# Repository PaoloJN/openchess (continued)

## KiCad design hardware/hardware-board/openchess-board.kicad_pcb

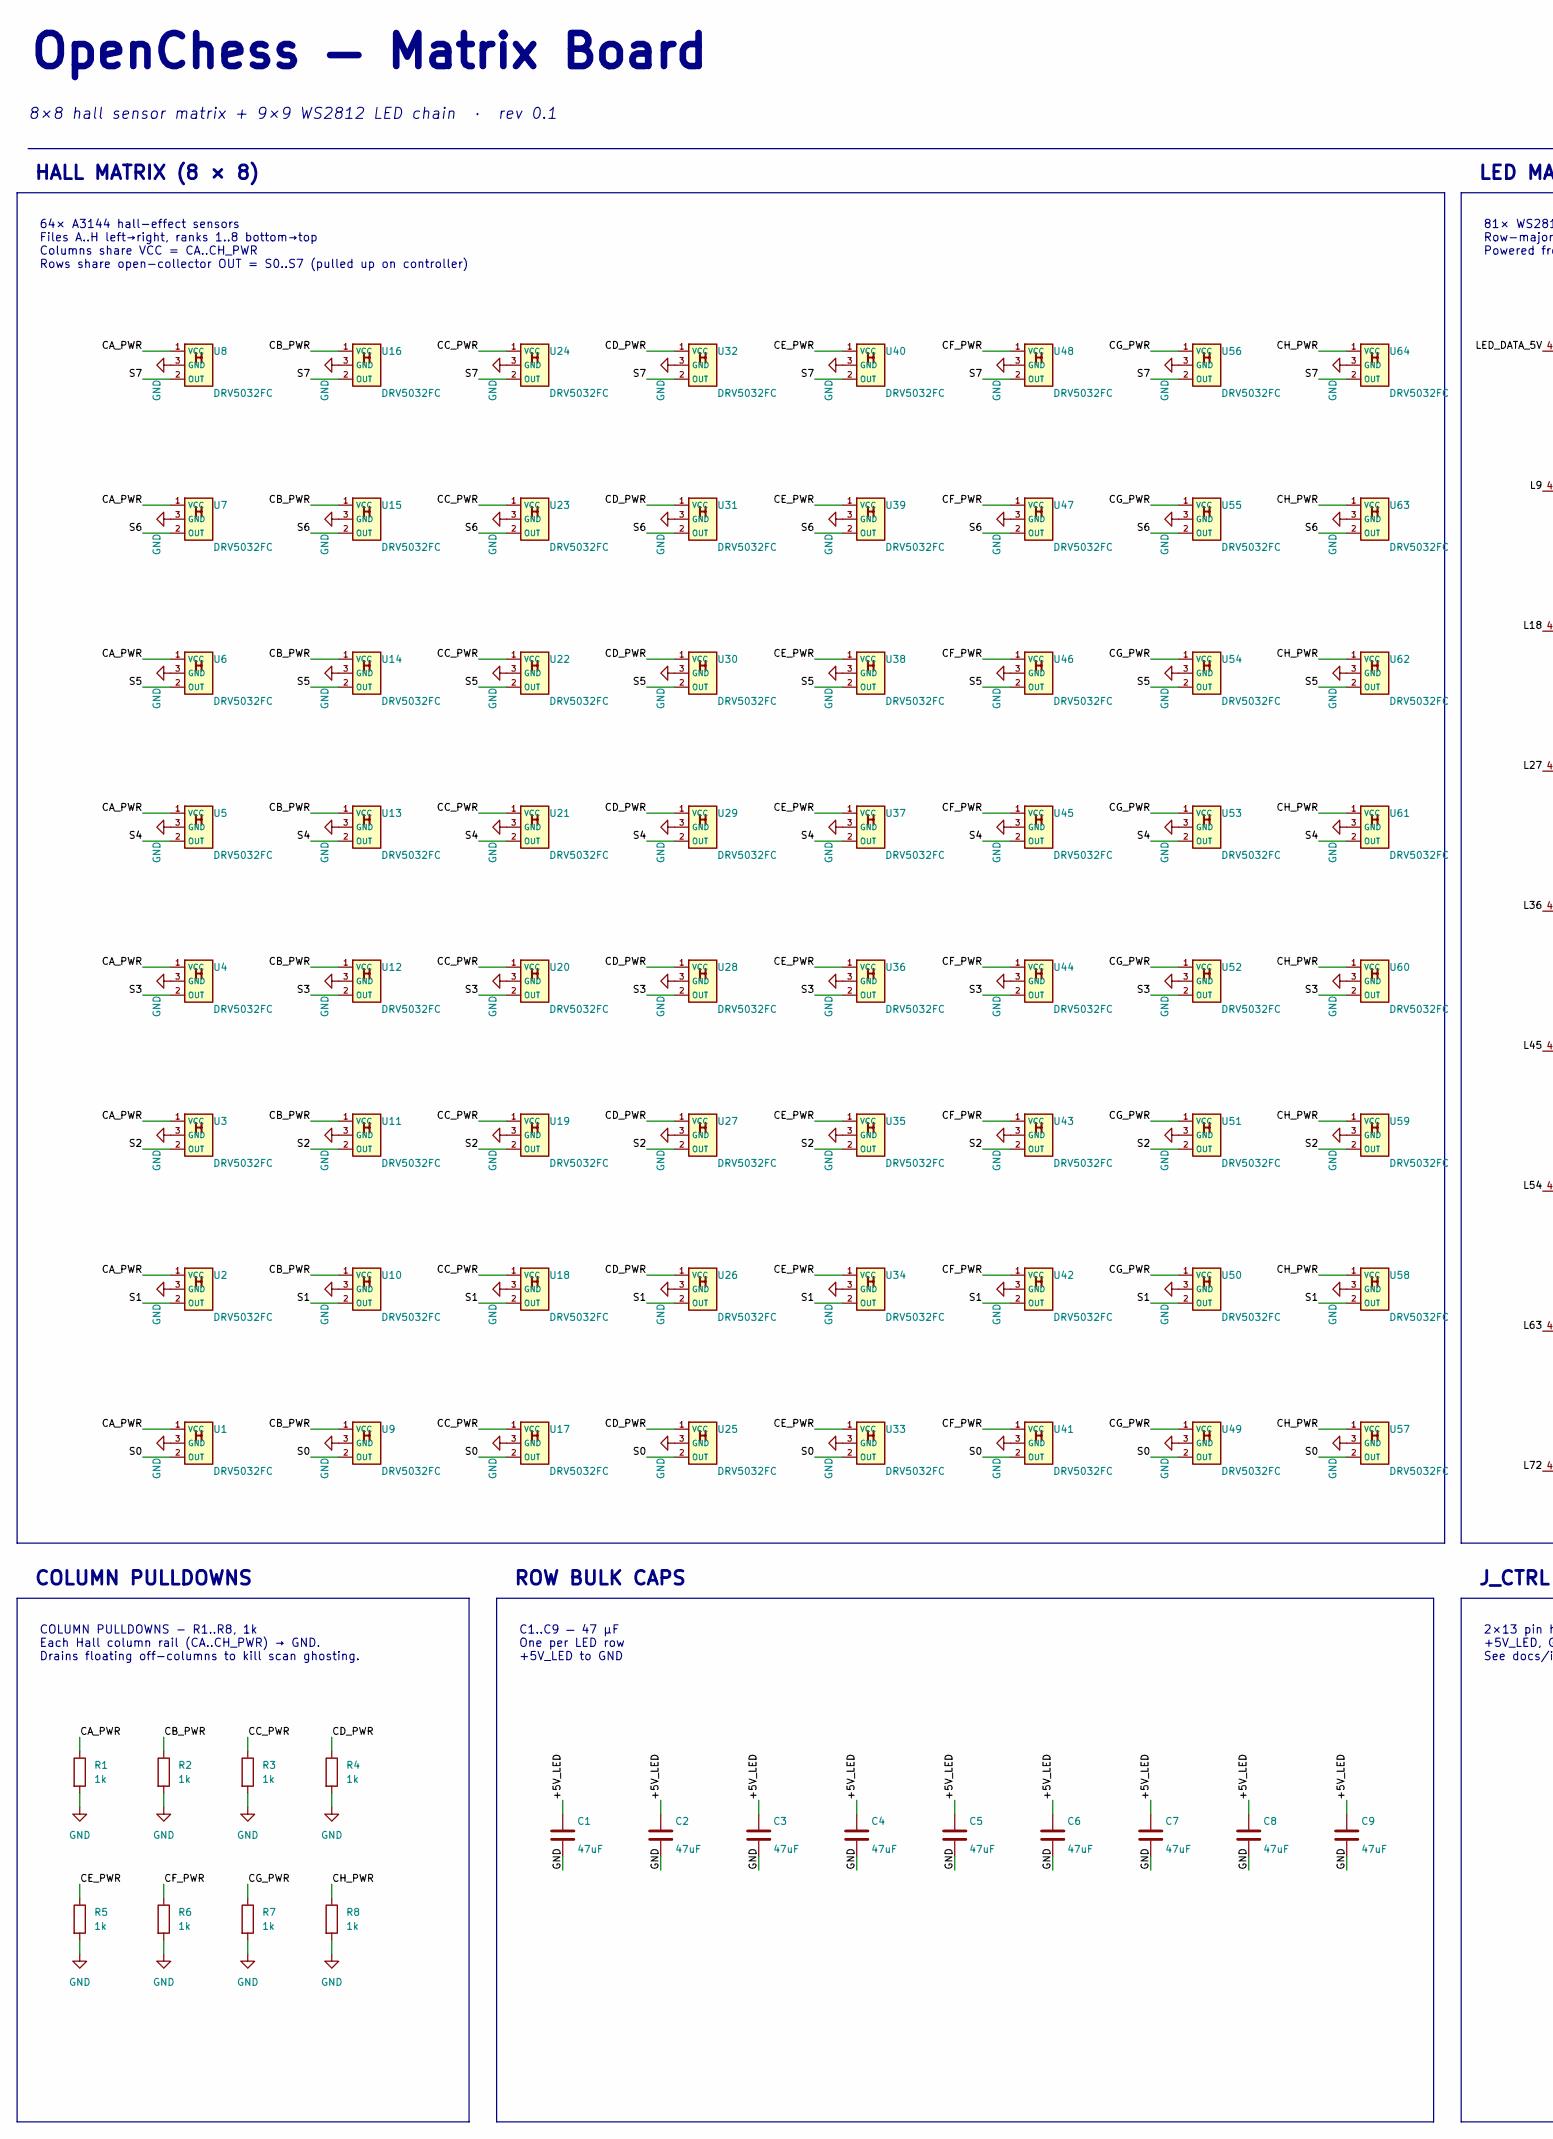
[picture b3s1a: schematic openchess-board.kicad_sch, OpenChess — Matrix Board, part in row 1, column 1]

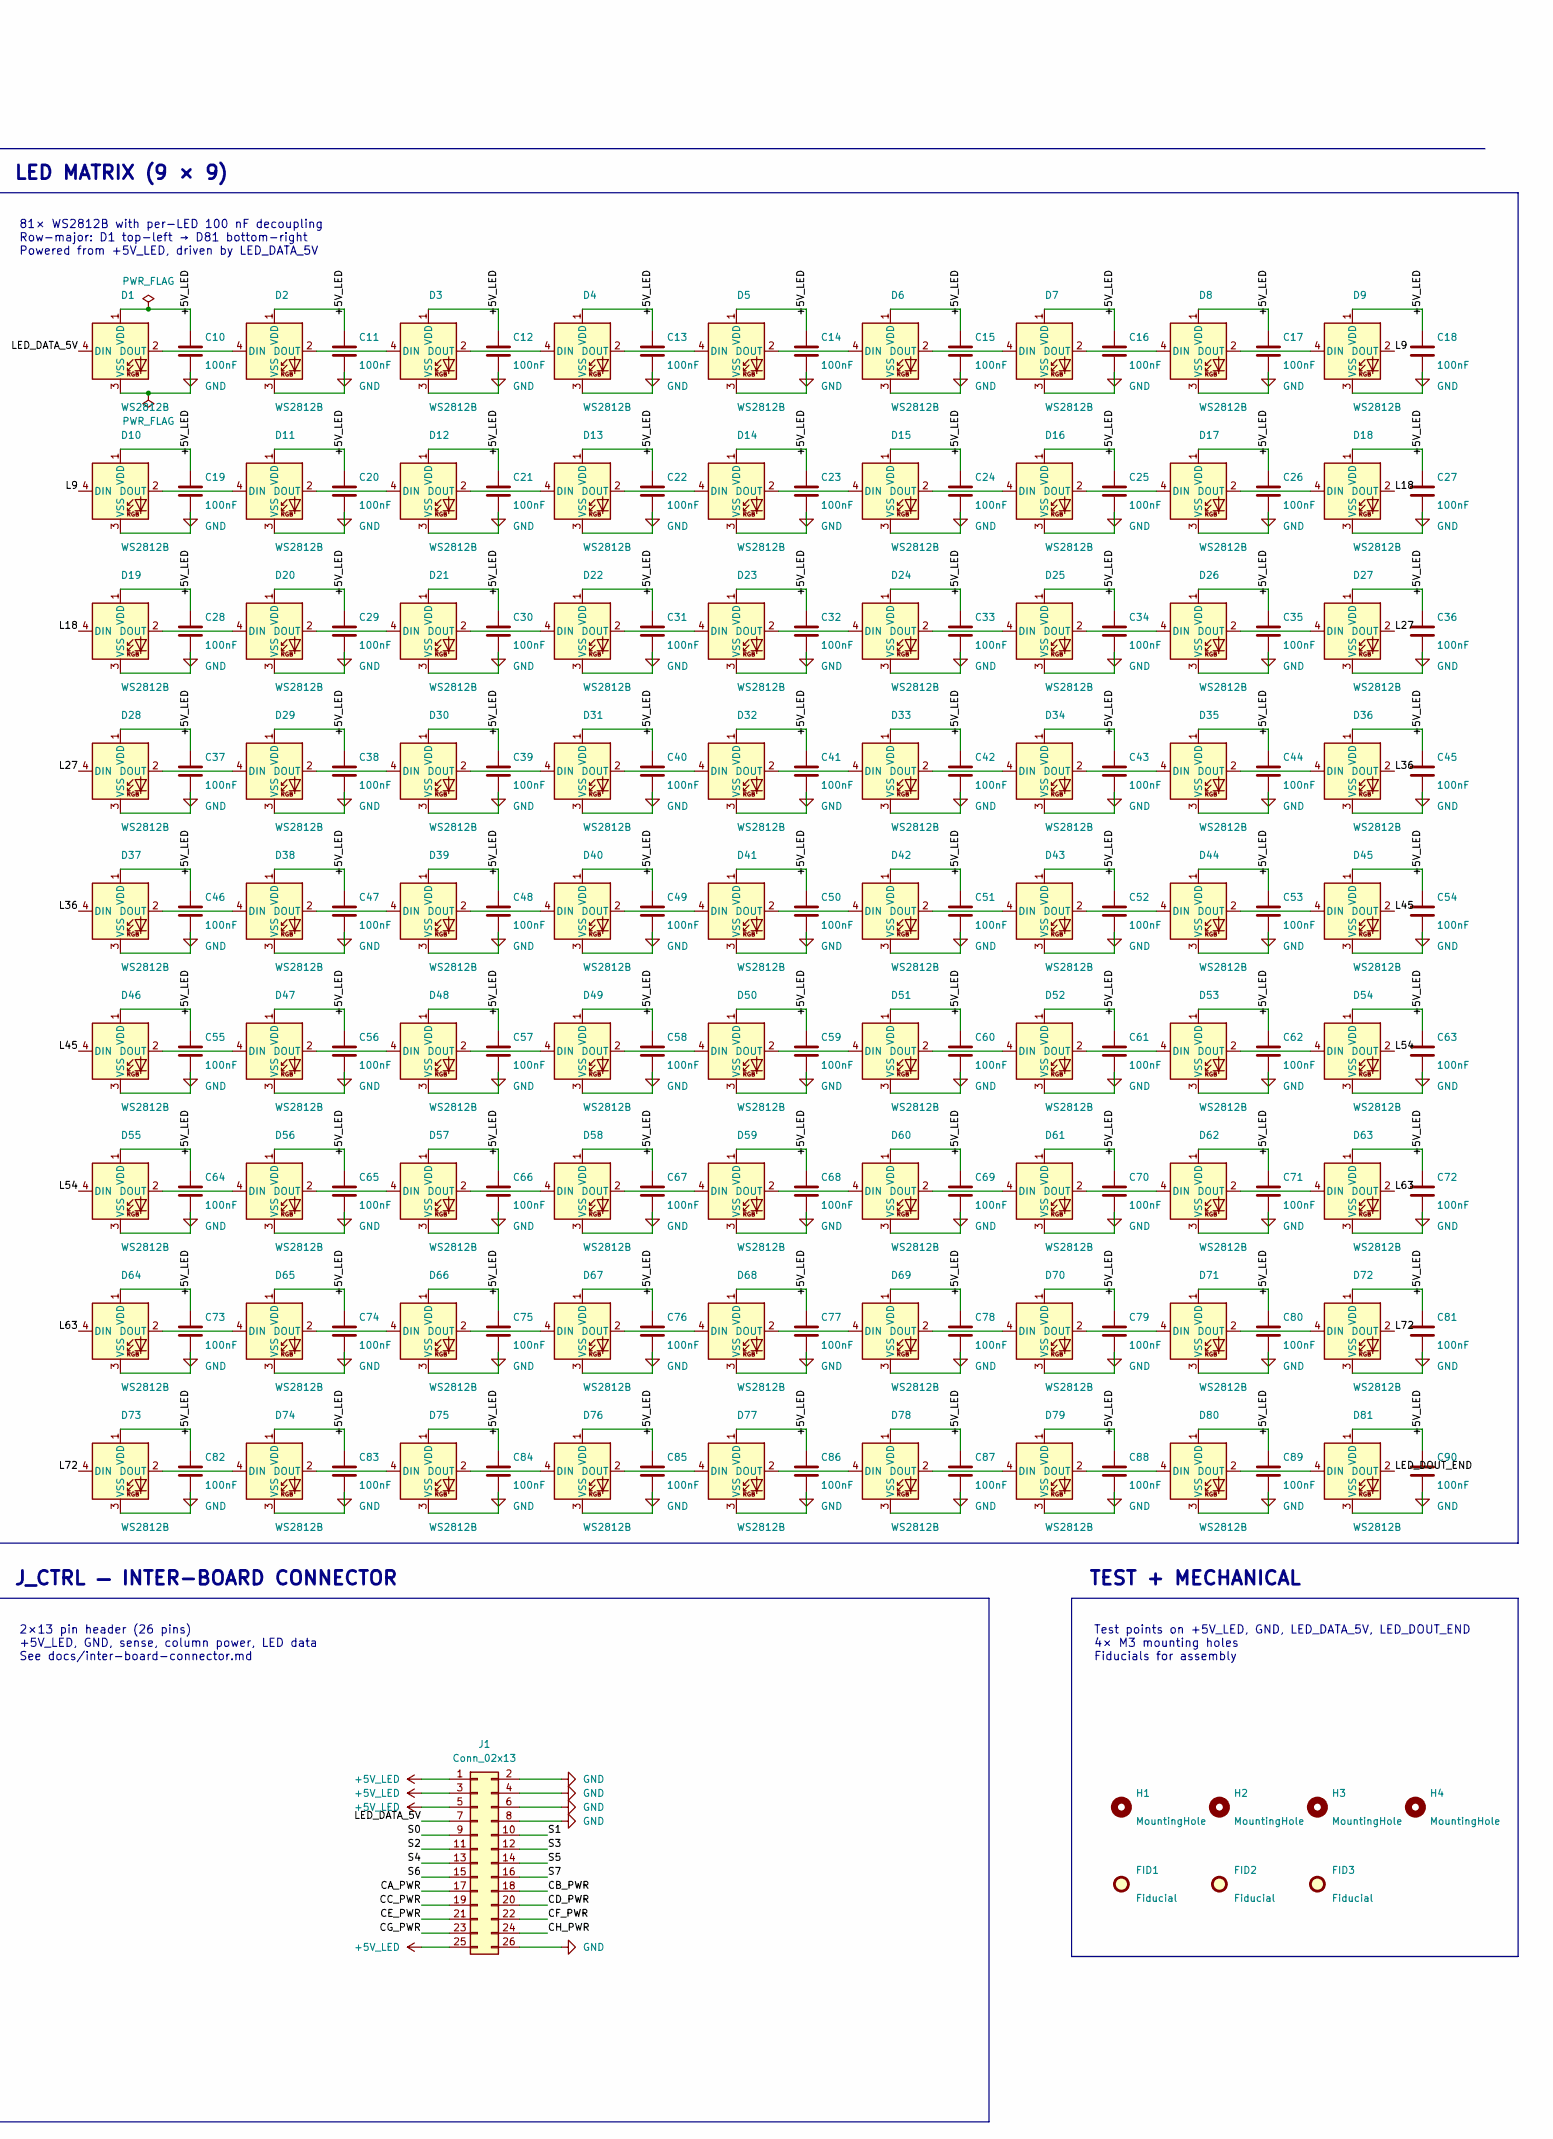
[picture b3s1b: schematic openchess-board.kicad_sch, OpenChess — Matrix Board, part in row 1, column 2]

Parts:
C1, C2, C3, C4, C5, C6, C7, C8, C9: 47uF; C_1206_3216Metric
C10, C11, C12, C13, C14, C15, C16, C17, C18, C19, C20, C21, C22, C23, C24, C25, C26, C27, C28, C29, C30, C31, C32, C33, C34, C35, C36, C37, C38, C39, C40, C41, C42, C43, C44, C45, C46, C47, C48, C49, C50, C51, C52, C53, C54, C55, C56, C57, C58, C59, C60, C61, C62, C63, C64, C65, C66, C67, C68, C69, C70, C71, C72, C73, C74, C75, C76, C77, C78, C79, C80, C81, C82, C83, C84, C85, C86, C87, C88, C89, C90: 100nF; C_0805_2012Metric_Pad1.18x1.45mm_HandSolder
D1, D2, D3, D4, D5, D6, D7, D8, D9, D10, D11, D12, D13, D14, D15, D16, D17, D18, D19, D20, D21, D22, D23, D24, D25, D26, D27, D28, D29, D30, D31, D32, D33, D34, D35, D36, D37, D38, D39, D40, D41, D42, D43, D44, D45, D46, D47, D48, D49, D50, D51, D52, D53, D54, D55, D56, D57, D58, D59, D60, D61, D62, D63, D64, D65, D66, D67, D68, D69, D70, D71, D72, D73, D74, D75, D76, D77, D78, D79, D80, D81: WS2812B; LED_WS2812B_PLCC4_5.0x5.0mm_P3.2mm
FID1, FID2, FID3: Fiducial; Fiducial_1mm_Mask2mm
H1, H2, H3, H4: MountingHole; MountingHole_3.2mm_M3
J1: Conn_02x13; PinHeader_2x13_P2.54mm_Vertical
R1, R2, R3, R4, R5, R6, R7, R8: 1k; R_0805_2012Metric_Pad1.20x1.40mm_HandSolder
U1, U2, U3, U4, U5, U6, U7, U8, U9, U10, U11, U12, U13, U14, U15, U16, U17, U18, U19, U20, U21, U22, U23, U24, U25, U26, U27, U28, U29, U30, U31, U32, U33, U34, U35, U36, U37, U38, U39, U40, U41, U42, U43, U44, U45, U46, U47, U48, U49, U50, U51, U52, U53, U54, U55, U56, U57, U58, U59, U60, U61, U62, U63, U64: DRV5032FC; SOT-23

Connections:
+5V_LED: C1.1, C2.1, C3.1, C4.1, C5.1, C6.1, C7.1, C8.1, C9.1, C10.1, C11.1, C12.1, C13.1, C14.1, C15.1, C16.1, C17.1, C18.1, C19.1, C20.1, C21.1, C22.1, C23.1, C24.1, C25.1, C26.1, C27.1, C28.1, C29.1, C30.1, C31.1, C32.1, C33.1, C34.1, C35.1, C36.1, C37.1, C38.1, C39.1, C40.1, C41.1, C42.1, C43.1, C44.1, C45.1, C46.1, C47.1, C48.1, C49.1, C50.1, C51.1, C52.1, C53.1, C54.1, C55.1, C56.1, C57.1, C58.1, C59.1, C60.1, C61.1, C62.1, C63.1, C64.1, C65.1, C66.1, C67.1, C68.1, C69.1, C70.1, C71.1, C72.1, C73.1, C74.1, C75.1, C76.1, C77.1, C78.1, C79.1, C80.1, C81.1, C82.1, C83.1, C84.1, C85.1, C86.1, C87.1, C88.1, C89.1, C90.1, D1.1 (VDD), D2.1 (VDD), D3.1 (VDD), D4.1 (VDD), D5.1 (VDD), D6.1 (VDD), D7.1 (VDD), D8.1 (VDD), D9.1 (VDD), D10.1 (VDD), D11.1 (VDD), D12.1 (VDD), D13.1 (VDD), D14.1 (VDD), D15.1 (VDD), D16.1 (VDD), D17.1 (VDD), D18.1 (VDD), D19.1 (VDD), D20.1 (VDD), D21.1 (VDD), D22.1 (VDD), D23.1 (VDD), D24.1 (VDD), D25.1 (VDD), D26.1 (VDD), D27.1 (VDD), D28.1 (VDD), D29.1 (VDD), D30.1 (VDD), D31.1 (VDD), D32.1 (VDD), D33.1 (VDD), D34.1 (VDD), D35.1 (VDD), D36.1 (VDD), D37.1 (VDD), D38.1 (VDD), D39.1 (VDD), D40.1 (VDD), D41.1 (VDD), D42.1 (VDD), D43.1 (VDD), D44.1 (VDD), D45.1 (VDD), D46.1 (VDD), D47.1 (VDD), D48.1 (VDD), D49.1 (VDD), D50.1 (VDD), D51.1 (VDD), D52.1 (VDD), D53.1 (VDD), D54.1 (VDD), D55.1 (VDD), D56.1 (VDD), D57.1 (VDD), D58.1 (VDD), D59.1 (VDD), D60.1 (VDD), D61.1 (VDD), D62.1 (VDD), D63.1 (VDD), D64.1 (VDD), D65.1 (VDD), D66.1 (VDD), D67.1 (VDD), D68.1 (VDD), D69.1 (VDD), D70.1 (VDD), D71.1 (VDD), D72.1 (VDD), D73.1 (VDD), D74.1 (VDD), D75.1 (VDD), D76.1 (VDD), D77.1 (VDD), D78.1 (VDD), D79.1 (VDD), D80.1 (VDD), D81.1 (VDD), J1.1, J1.3, J1.5, J1.25
/CA_PWR: J1.17, R1.1, U1.1 (VCC), U2.1 (VCC), U3.1 (VCC), U4.1 (VCC), U5.1 (VCC), U6.1 (VCC), U7.1 (VCC), U8.1 (VCC)
/CB_PWR: J1.18, R2.1, U9.1 (VCC), U10.1 (VCC), U11.1 (VCC), U12.1 (VCC), U13.1 (VCC), U14.1 (VCC), U15.1 (VCC), U16.1 (VCC)
/CC_PWR: J1.19, R3.1, U17.1 (VCC), U18.1 (VCC), U19.1 (VCC), U20.1 (VCC), U21.1 (VCC), U22.1 (VCC), U23.1 (VCC), U24.1 (VCC)
/CD_PWR: J1.20, R4.1, U25.1 (VCC), U26.1 (VCC), U27.1 (VCC), U28.1 (VCC), U29.1 (VCC), U30.1 (VCC), U31.1 (VCC), U32.1 (VCC)
/CE_PWR: J1.21, R5.1, U33.1 (VCC), U34.1 (VCC), U35.1 (VCC), U36.1 (VCC), U37.1 (VCC), U38.1 (VCC), U39.1 (VCC), U40.1 (VCC)
/CF_PWR: J1.22, R6.1, U41.1 (VCC), U42.1 (VCC), U43.1 (VCC), U44.1 (VCC), U45.1 (VCC), U46.1 (VCC), U47.1 (VCC), U48.1 (VCC)
/CG_PWR: J1.23, R7.1, U49.1 (VCC), U50.1 (VCC), U51.1 (VCC), U52.1 (VCC), U53.1 (VCC), U54.1 (VCC), U55.1 (VCC), U56.1 (VCC)
/CH_PWR: J1.24, R8.1, U57.1 (VCC), U58.1 (VCC), U59.1 (VCC), U60.1 (VCC), U61.1 (VCC), U62.1 (VCC), U63.1 (VCC), U64.1 (VCC)
/L9: D9.2 (DOUT), D10.4 (DIN)
/L18: D18.2 (DOUT), D19.4 (DIN)
/L27: D27.2 (DOUT), D28.4 (DIN)
/L36: D36.2 (DOUT), D37.4 (DIN)
/L45: D45.2 (DOUT), D46.4 (DIN)
/L54: D54.2 (DOUT), D55.4 (DIN)
/L63: D63.2 (DOUT), D64.4 (DIN)
/L72: D72.2 (DOUT), D73.4 (DIN)
/LED_DATA_5V: D1.4 (DIN), J1.7
/LED_DOUT_END: D81.2 (DOUT)
/S0: J1.9, U1.2 (OUT), U9.2 (OUT), U17.2 (OUT), U25.2 (OUT), U33.2 (OUT), U41.2 (OUT), U49.2 (OUT), U57.2 (OUT)
/S1: J1.10, U2.2 (OUT), U10.2 (OUT), U18.2 (OUT), U26.2 (OUT), U34.2 (OUT), U42.2 (OUT), U50.2 (OUT), U58.2 (OUT)
/S2: J1.11, U3.2 (OUT), U11.2 (OUT), U19.2 (OUT), U27.2 (OUT), U35.2 (OUT), U43.2 (OUT), U51.2 (OUT), U59.2 (OUT)
/S3: J1.12, U4.2 (OUT), U12.2 (OUT), U20.2 (OUT), U28.2 (OUT), U36.2 (OUT), U44.2 (OUT), U52.2 (OUT), U60.2 (OUT)
/S4: J1.13, U5.2 (OUT), U13.2 (OUT), U21.2 (OUT), U29.2 (OUT), U37.2 (OUT), U45.2 (OUT), U53.2 (OUT), U61.2 (OUT)
/S5: J1.14, U6.2 (OUT), U14.2 (OUT), U22.2 (OUT), U30.2 (OUT), U38.2 (OUT), U46.2 (OUT), U54.2 (OUT), U62.2 (OUT)
/S6: J1.15, U7.2 (OUT), U15.2 (OUT), U23.2 (OUT), U31.2 (OUT), U39.2 (OUT), U47.2 (OUT), U55.2 (OUT), U63.2 (OUT)
/S7: J1.16, U8.2 (OUT), U16.2 (OUT), U24.2 (OUT), U32.2 (OUT), U40.2 (OUT), U48.2 (OUT), U56.2 (OUT), U64.2 (OUT)
GND: C1.2, C2.2, C3.2, C4.2, C5.2, C6.2, C7.2, C8.2, C9.2, C10.2, C11.2, C12.2, C13.2, C14.2, C15.2, C16.2, C17.2, C18.2, C19.2, C20.2, C21.2, C22.2, C23.2, C24.2, C25.2, C26.2, C27.2, C28.2, C29.2, C30.2, C31.2, C32.2, C33.2, C34.2, C35.2, C36.2, C37.2, C38.2, C39.2, C40.2, C41.2, C42.2, C43.2, C44.2, C45.2, C46.2, C47.2, C48.2, C49.2, C50.2, C51.2, C52.2, C53.2, C54.2, C55.2, C56.2, C57.2, C58.2, C59.2, C60.2, C61.2, C62.2, C63.2, C64.2, C65.2, C66.2, C67.2, C68.2, C69.2, C70.2, C71.2, C72.2, C73.2, C74.2, C75.2, C76.2, C77.2, C78.2, C79.2, C80.2, C81.2, C82.2, C83.2, C84.2, C85.2, C86.2, C87.2, C88.2, C89.2, C90.2, D1.3 (VSS), D2.3 (VSS), D3.3 (VSS), D4.3 (VSS), D5.3 (VSS), D6.3 (VSS), D7.3 (VSS), D8.3 (VSS), D9.3 (VSS), D10.3 (VSS), D11.3 (VSS), D12.3 (VSS), D13.3 (VSS), D14.3 (VSS), D15.3 (VSS), D16.3 (VSS), D17.3 (VSS), D18.3 (VSS), D19.3 (VSS), D20.3 (VSS), D21.3 (VSS), D22.3 (VSS), D23.3 (VSS), D24.3 (VSS), D25.3 (VSS), D26.3 (VSS), D27.3 (VSS), D28.3 (VSS), D29.3 (VSS), D30.3 (VSS), D31.3 (VSS), D32.3 (VSS), D33.3 (VSS), D34.3 (VSS), D35.3 (VSS), D36.3 (VSS), D37.3 (VSS), D38.3 (VSS), D39.3 (VSS), D40.3 (VSS), D41.3 (VSS), D42.3 (VSS), D43.3 (VSS), D44.3 (VSS), D45.3 (VSS), D46.3 (VSS), D47.3 (VSS), D48.3 (VSS), D49.3 (VSS), D50.3 (VSS), D51.3 (VSS), D52.3 (VSS), D53.3 (VSS), D54.3 (VSS), D55.3 (VSS), D56.3 (VSS), D57.3 (VSS), D58.3 (VSS), D59.3 (VSS), D60.3 (VSS), D61.3 (VSS), D62.3 (VSS), D63.3 (VSS), D64.3 (VSS), D65.3 (VSS), D66.3 (VSS), D67.3 (VSS), D68.3 (VSS), D69.3 (VSS), D70.3 (VSS), D71.3 (VSS), D72.3 (VSS), D73.3 (VSS), D74.3 (VSS), D75.3 (VSS), D76.3 (VSS), D77.3 (VSS), D78.3 (VSS), D79.3 (VSS), D80.3 (VSS), D81.3 (VSS), J1.2, J1.4, J1.6, J1.8, J1.26, R1.2, R2.2, R3.2, R4.2, R5.2, R6.2, R7.2, R8.2, U1.3 (GND), U2.3 (GND), U3.3 (GND), U4.3 (GND), U5.3 (GND), U6.3 (GND), U7.3 (GND), U8.3 (GND), U9.3 (GND), U10.3 (GND), U11.3 (GND), U12.3 (GND), U13.3 (GND), U14.3 (GND), U15.3 (GND), U16.3 (GND), U17.3 (GND), U18.3 (GND), U19.3 (GND), U20.3 (GND), U21.3 (GND), U22.3 (GND), U23.3 (GND), U24.3 (GND), U25.3 (GND), U26.3 (GND), U27.3 (GND), U28.3 (GND), U29.3 (GND), U30.3 (GND), U31.3 (GND), U32.3 (GND), U33.3 (GND), U34.3 (GND), U35.3 (GND), U36.3 (GND), U37.3 (GND), U38.3 (GND), U39.3 (GND), U40.3 (GND), U41.3 (GND), U42.3 (GND), U43.3 (GND), U44.3 (GND), U45.3 (GND), U46.3 (GND), U47.3 (GND), U48.3 (GND), U49.3 (GND), U50.3 (GND), U51.3 (GND), U52.3 (GND), U53.3 (GND), U54.3 (GND), U55.3 (GND), U56.3 (GND), U57.3 (GND), U58.3 (GND), U59.3 (GND), U60.3 (GND), U61.3 (GND), U62.3 (GND), U63.3 (GND), U64.3 (GND)
unnamed: D1.2 (DOUT), D2.4 (DIN)
unnamed: D2.2 (DOUT), D3.4 (DIN)
unnamed: D3.2 (DOUT), D4.4 (DIN)
unnamed: D4.2 (DOUT), D5.4 (DIN)
unnamed: D5.2 (DOUT), D6.4 (DIN)
unnamed: D6.2 (DOUT), D7.4 (DIN)
unnamed: D7.2 (DOUT), D8.4 (DIN)
unnamed: D8.2 (DOUT), D9.4 (DIN)
unnamed: D10.2 (DOUT), D11.4 (DIN)
unnamed: D11.2 (DOUT), D12.4 (DIN)
unnamed: D12.2 (DOUT), D13.4 (DIN)
unnamed: D13.2 (DOUT), D14.4 (DIN)
unnamed: D14.2 (DOUT), D15.4 (DIN)
unnamed: D15.2 (DOUT), D16.4 (DIN)
unnamed: D16.2 (DOUT), D17.4 (DIN)
unnamed: D17.2 (DOUT), D18.4 (DIN)
unnamed: D19.2 (DOUT), D20.4 (DIN)
unnamed: D20.2 (DOUT), D21.4 (DIN)
unnamed: D21.2 (DOUT), D22.4 (DIN)
unnamed: D22.2 (DOUT), D23.4 (DIN)
unnamed: D23.2 (DOUT), D24.4 (DIN)
unnamed: D24.2 (DOUT), D25.4 (DIN)
unnamed: D25.2 (DOUT), D26.4 (DIN)
unnamed: D26.2 (DOUT), D27.4 (DIN)
unnamed: D28.2 (DOUT), D29.4 (DIN)
unnamed: D29.2 (DOUT), D30.4 (DIN)
unnamed: D30.2 (DOUT), D31.4 (DIN)
unnamed: D31.2 (DOUT), D32.4 (DIN)
unnamed: D32.2 (DOUT), D33.4 (DIN)
unnamed: D33.2 (DOUT), D34.4 (DIN)
unnamed: D34.2 (DOUT), D35.4 (DIN)
unnamed: D35.2 (DOUT), D36.4 (DIN)
unnamed: D37.2 (DOUT), D38.4 (DIN)
unnamed: D38.2 (DOUT), D39.4 (DIN)
unnamed: D39.2 (DOUT), D40.4 (DIN)
unnamed: D40.2 (DOUT), D41.4 (DIN)
unnamed: D41.2 (DOUT), D42.4 (DIN)
unnamed: D42.2 (DOUT), D43.4 (DIN)
unnamed: D43.2 (DOUT), D44.4 (DIN)
unnamed: D44.2 (DOUT), D45.4 (DIN)
unnamed: D46.2 (DOUT), D47.4 (DIN)
unnamed: D47.2 (DOUT), D48.4 (DIN)
unnamed: D48.2 (DOUT), D49.4 (DIN)
unnamed: D49.2 (DOUT), D50.4 (DIN)
unnamed: D50.2 (DOUT), D51.4 (DIN)
unnamed: D51.2 (DOUT), D52.4 (DIN)
unnamed: D52.2 (DOUT), D53.4 (DIN)
unnamed: D53.2 (DOUT), D54.4 (DIN)
unnamed: D55.2 (DOUT), D56.4 (DIN)
unnamed: D56.2 (DOUT), D57.4 (DIN)
unnamed: D57.2 (DOUT), D58.4 (DIN)
unnamed: D58.2 (DOUT), D59.4 (DIN)
unnamed: D59.2 (DOUT), D60.4 (DIN)
unnamed: D60.2 (DOUT), D61.4 (DIN)
unnamed: D61.2 (DOUT), D62.4 (DIN)
unnamed: D62.2 (DOUT), D63.4 (DIN)
unnamed: D64.2 (DOUT), D65.4 (DIN)
unnamed: D65.2 (DOUT), D66.4 (DIN)
unnamed: D66.2 (DOUT), D67.4 (DIN)
unnamed: D67.2 (DOUT), D68.4 (DIN)
unnamed: D68.2 (DOUT), D69.4 (DIN)
unnamed: D69.2 (DOUT), D70.4 (DIN)
unnamed: D70.2 (DOUT), D71.4 (DIN)
unnamed: D71.2 (DOUT), D72.4 (DIN)
unnamed: D73.2 (DOUT), D74.4 (DIN)
unnamed: D74.2 (DOUT), D75.4 (DIN)
unnamed: D75.2 (DOUT), D76.4 (DIN)
unnamed: D76.2 (DOUT), D77.4 (DIN)
unnamed: D77.2 (DOUT), D78.4 (DIN)
unnamed: D78.2 (DOUT), D79.4 (DIN)
unnamed: D79.2 (DOUT), D80.4 (DIN)
unnamed: D80.2 (DOUT), D81.4 (DIN)

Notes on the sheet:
OpenChess — Matrix Board
8×8 hall sensor matrix + 9×9 WS2812 LED chain · rev 0.1
HALL MATRIX (8 × 8)
64× A3144 hall-effect sensors Files A..H left→right, ranks 1..8 bottom→top Columns share VCC = CA..CH_PWR Rows share open-collector OUT = S0..S7 (pulled up on controller)
LED MATRIX (9 × 9)
81× WS2812B with per-LED 100 nF decoupling Row-major: D1 top-left → D81 bottom-right Powered from +5V_LED, driven by LED_DATA_5V
COLUMN PULLDOWNS
COLUMN PULLDOWNS - R1..R8, 1k Each Hall column rail (CA..CH_PWR) → GND. Drains floating off-columns to kill scan ghosting.
ROW BULK CAPS
C1..C9 — 47 µF One per LED row +5V_LED to GND
J_CTRL — INTER-BOARD CONNECTOR
2×13 pin header (26 pins) +5V_LED, GND, sense, column power, LED data See docs/inter-board-connector.md
TEST + MECHANICAL
Test points on +5V_LED, GND, LED_DATA_5V, LED_DOUT_END 4× M3 mounting holes Fiducials for assembly

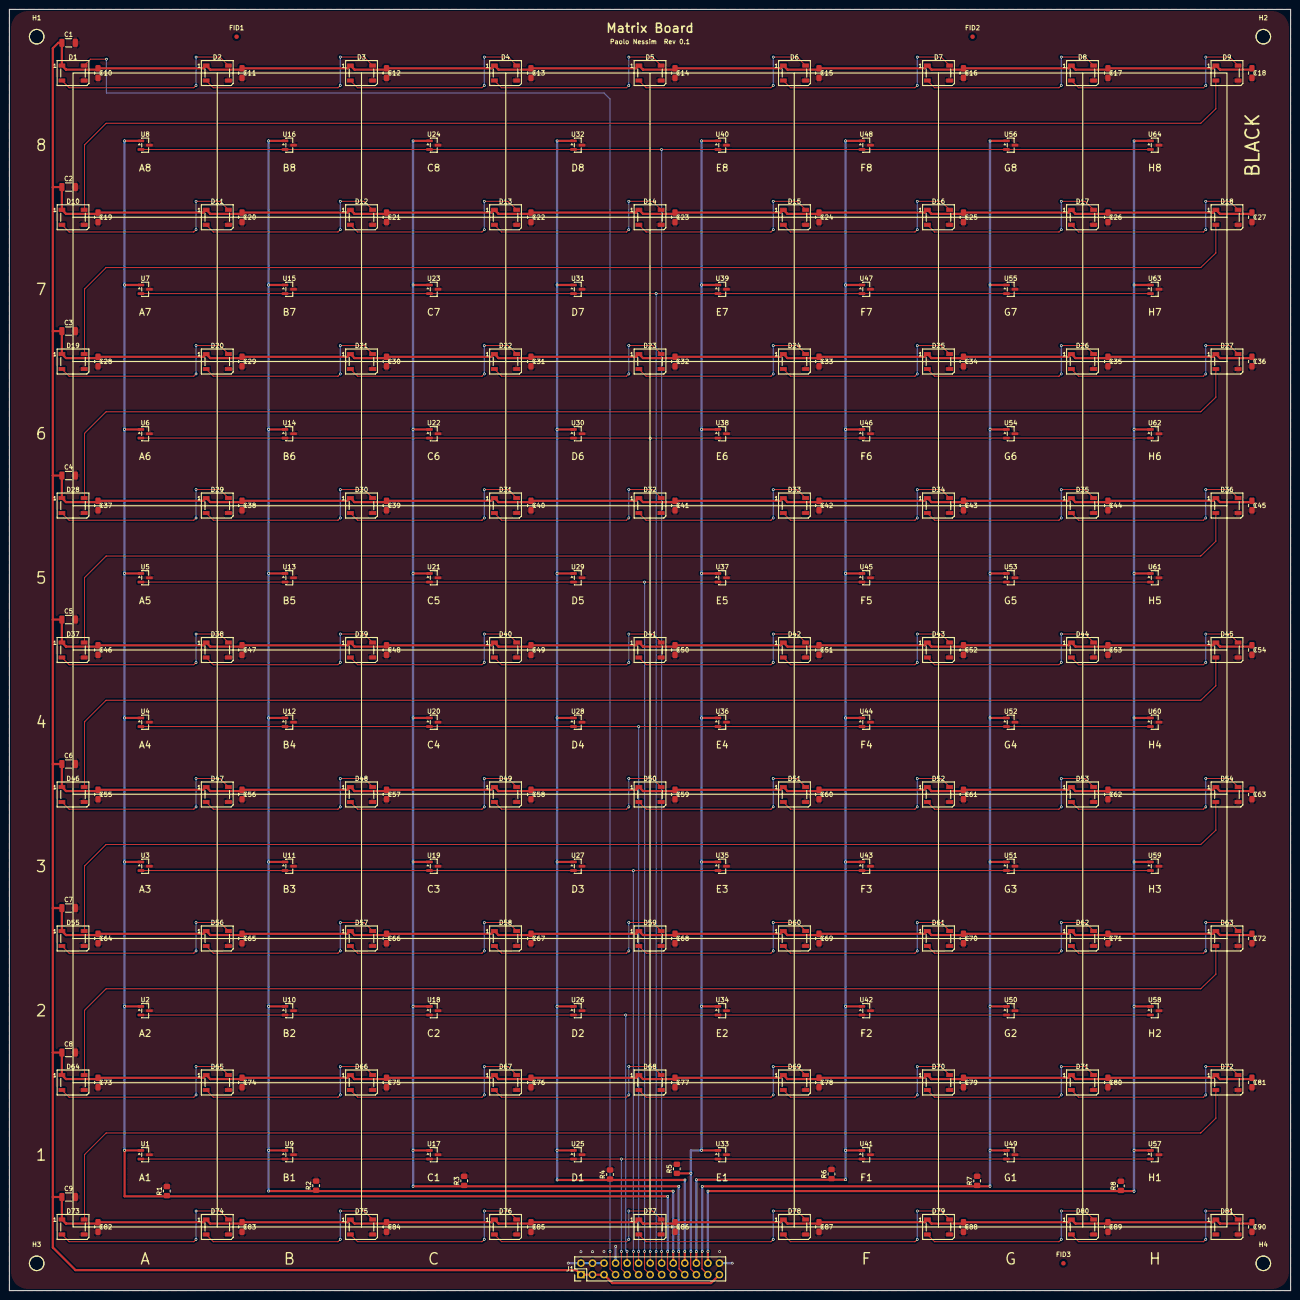
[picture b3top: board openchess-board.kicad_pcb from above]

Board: 2 copper layers, 282.0 x 282.0 mm, 251 parts (1 on the bottom side), 99 nets.

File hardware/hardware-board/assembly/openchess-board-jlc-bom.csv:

Comment,Designator,Footprint,JLCPCB Part #
47uF,"C1,C2,C3,C4,C5,C6,C7,C8,C9",1206,C96123
100nF,"C10,C11,C12,C13,C14,C15,C16,C17,C18,C19,C20,C21,C22,C23,C24,C25,C26,C27,C28,C29,C30,C31,C32,C33,C34,C35,C36,C37,C38,C39,C40,C41,C42,C43,C44,C45,C46,C47,C48,C49,C50,C51,C52,C53,C54,C55,C56,C57,C58,C59,C60,C61,C62,C63,C64,C65,C66,C67,C68,C69,C70,C71,C72,C73,C74,C75,C76,C77,C78,C79,C80,C81,C82,C83,C84,C85,C86,C87,C88,C89,C90",0805,C49678
WS2812B,"D1,D2,D3,D4,D5,D6,D7,D8,D9,D10,D11,D12,D13,D14,D15,D16,D17,D18,D19,D20,D21,D22,D23,D24,D25,D26,D27,D28,D29,D30,D31,D32,D33,D34,D35,D36,D37,D38,D39,D40,D41,D42,D43,D44,D45,D46,D47,D48,D49,D50,D51,D52,D53,D54,D55,D56,D57,D58,D59,D60,D61,D62,D63,D64,D65,D66,D67,D68,D69,D70,D71,D72,D73,D74,D75,D76,D77,D78,D79,D80,D81",LED-WS2812B-PLCC4-5.0x5.0,C2761795
1k,"R1,R2,R3,R4,R5,R6,R7,R8",0805,C17513
DRV5032FC,"U1,U2,U3,U4,U5,U6,U7,U8,U9,U10,U11,U12,U13,U14,U15,U16,U17,U18,U19,U20,U21,U22,U23,U24,U25,U26,U27,U28,U29,U30,U31,U32,U33,U34,U35,U36,U37,U38,U39,U40,U41,U42,U43,U44,U45,U46,U47,U48,U49,U50,U51,U52,U53,U54,U55,U56,U57,U58,U59,U60,U61,U62,U63,U64",SOT-23,C527532

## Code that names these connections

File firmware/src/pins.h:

// pins.h — OpenChess controller GPIO map (v0.1 hardware)
// Extracted from hardware-controller/openchess-controller.kicad_sch — the real board.
// Do not guess pins; this is the source of truth.
#pragma once

// ── LED chain (WS2812B) ───────────────────────────────────────────────
// Data goes 3.3V GPIO -> 74AHCT125 level shifter -> 5V -> J1 -> matrix D1..D81.
#define PIN_LED_DATA       32   // GPIO32  (/LED_DATA)

// ── Matrix column drive (high-side via TBD62783A) ─────────────────────
// One column powered at a time. Order A..H = files A..H.
static const int PIN_COL_DRV[8] = {
    13,  // A  GPIO13 (/COL_DRV_A)
    14,  // B  GPIO14 (/COL_DRV_B)
    27,  // C  GPIO27 (/COL_DRV_C)
    26,  // D  GPIO26 (/COL_DRV_D)
    25,  // E  GPIO25 (/COL_DRV_E)
    33,  // F  GPIO33 (/COL_DRV_F)
     5,  // G  GPIO5  (/COL_DRV_G)   *strapping pin — OK, internal pull-up high at boot
    15,  // H  GPIO15 (/COL_DRV_H)   *strapping pin — OK
};

// ── Matrix row sense (hall OUT, open-drain, pulled up to 3.3V) ─────────
// S0..S7 = ranks. Read these while a column is powered. (digital inputs)
static const int PIN_ROW_SENSE[8] = {
     4,  // S0  GPIO4
    16,  // S1  GPIO16
    17,  // S2  GPIO17
    18,  // S3  GPIO18
    19,  // S4  GPIO19
    21,  // S5  GPIO21
    22,  // S6  GPIO22
    23,  // S7  GPIO23
};

// ── Panel I2C (OLED SSD1306) ──────────────────────────────────────────
// NOTE: these are UART0 pins. Serial-over-USB and the OLED share them,
// so: (a) you can't use Serial debug while the OLED is connected, and
// (b) disconnect the OLED from these pins when flashing firmware.
#define PIN_I2C_SDA         1   // GPIO1  (U0TXD)
#define PIN_I2C_SCL         3   // GPIO3  (U0RXD)

// ── Panel buttons / rotary encoder ────────────────────────────────────
// Board originally wired for 3 buttons. If using a ROTARY ENCODER instead,
// wire it as noted below (A/B already have pull-ups via R36/R37).
#define PIN_BTN_POWER      36   // GPIO36 (input-only, ext pull-up R36)  | ENCODER A
#define PIN_BTN_MODE       39   // GPIO39 (input-only, ext pull-up R37)  | ENCODER B
#define PIN_BTN_SELECT      2   // GPIO2  (internal pull-up)             | ENCODER PUSH
#define PIN_PANEL_SPARE    35   // GPIO35 (input-only, NO pull-up)       | spare / power btn

// Functional mapping — use THESE in firmware, not the raw net names above.
// 2026-08 incident: a solder bridge between the GPIO2 and GPIO36 lines made
// OK presses read as DOWN *and* blocked download mode (GPIO2 is a strapping
// pin). If OK still acts as DOWN after the joints are fixed, the caps are
// cross-wired — just swap OK and DOWN here.
#define PIN_BTN_UP         PIN_BTN_MODE    // GPIO39, ext pull-up
#define PIN_BTN_DOWN       PIN_BTN_POWER   // GPIO36, ext pull-up R36
#define PIN_BTN_OK         PIN_BTN_SELECT  // GPIO2, needs INPUT_PULLUP

// ── Battery monitor ───────────────────────────────────────────────────
// Divider R14/R15 = 0.3125x. ADC1 (works during WiFi). 4.2V batt -> ~1.31V.
#define PIN_VBAT_MON       34   // GPIO34 (ADC1_CH6)

// ── Counts ────────────────────────────────────────────────────────────
#define MATRIX_COLS         8
#define MATRIX_ROWS         8
#define LED_COUNT          81   // 9x9 corners

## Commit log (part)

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2026-06-05 Add scripts for PCB layout and routing: grid placement, LED chain routing, and power planes
2026-06-06 Refactor code structure for improved readability and maintainability
2026-06-06 Add new mechanical and power symbols for schematic integration
    - Introduced new symbols: TestPoint, Fiducial, MountingHole, +3V3, and GND.
    - Each symbol includes properties for reference, value, footprint, datasheet, description, keywords, and filters.
    - Implemented a Python script to merge test/mech snippets into the main schematic, ensuring backup and validation of parens.
    - The script adds missing symbol definitions and integrates component instances, labels, wires, and power ports.
2026-06-06 Mark subproject commits as dirty in hardware board and controller histories
2026-06-07 Controller PCB: hand-routed power rails before autoroute
2026-06-07 Add PCB layout and schematic guides for OpenChess controller
    - Introduced `controller-PCB_LAYOUT_GUIDE.planning.md` detailing PCB layout constraints, component placement zones, net classes, routing priorities, and mechanical verification for the OpenChess cont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
    - Added `controller-SCHEMATIC_GUIDE.planning.md` providing a comprehensive schematic specification, including reference designators, net lists, component details, and validation rules for the OpenChe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
2026-06-07 Remove obsolete files and backups from hardware-controller project
    - Deleted the .history directory and its contents.
    - Removed all KiNotes markdown files and their backups.
    - Cleared settings, todos, and version log JSON files.
    - Eliminated the BOM CSV file for the openchess-controller.
2026-06-09 Add initial files for openchess board project
    - Created Gerber job file for openchess board with specifications and material stackup.
    - Added backup of the KiCad PCB file before modifications.
    - Introduced STEP files for the 3x3 chess board and the main chess controller.
    - Initialized notes file for project documentation.
2026-06-09 Add scripts to merge and tile PDF layers for KiCad projects
    - Implemented `merge_pdf_layers.py` to overlay multiple single-page PDFs into one page, allowing for easy printing of layered designs.
    - Created `tile_pdf_to_a4.py` to split large PDFs into A4-sized tiles with configurable overlap, facilitating printing on standard home printers.
    - Both scripts require the `pypdf` library for PDF manipulation.
2026-06-09 chore: update code structure and remove redundant sections
2026-06-12 Add JLCPCB BOM and CPL generation scripts for OpenChess board
    - Created openchess-board-jlc-bom.csv to define unique components with their specifications for JLCPCB.
    - Created openchess-board-jlc-cpl.csv to specify the placement of components on the board.
    - Implemented make_jlc_assembly.py script to automate the generation of BOM and CPL from KiCad's exported all-pos.csv.
    - The script handles Y-axis flipping and formats output according to JLCPCB requirements.
    - Excluded mechanical components from assembly files as per JLCPCB guidelines.
2026-06-12 docs: add project cleanup design spec
2026-06-12 docs: sync project docs with current board designs
2026-06-21 Add initial positions CSV for hardware components
    This commit introduces a new CSV file containing the designator, midpoints, rotation, and layer information for various hardware components used in the project. The data includes positions for capaci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
